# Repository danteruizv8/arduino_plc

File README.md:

# arduino_plc

Arduino compatible PLC board PCB.

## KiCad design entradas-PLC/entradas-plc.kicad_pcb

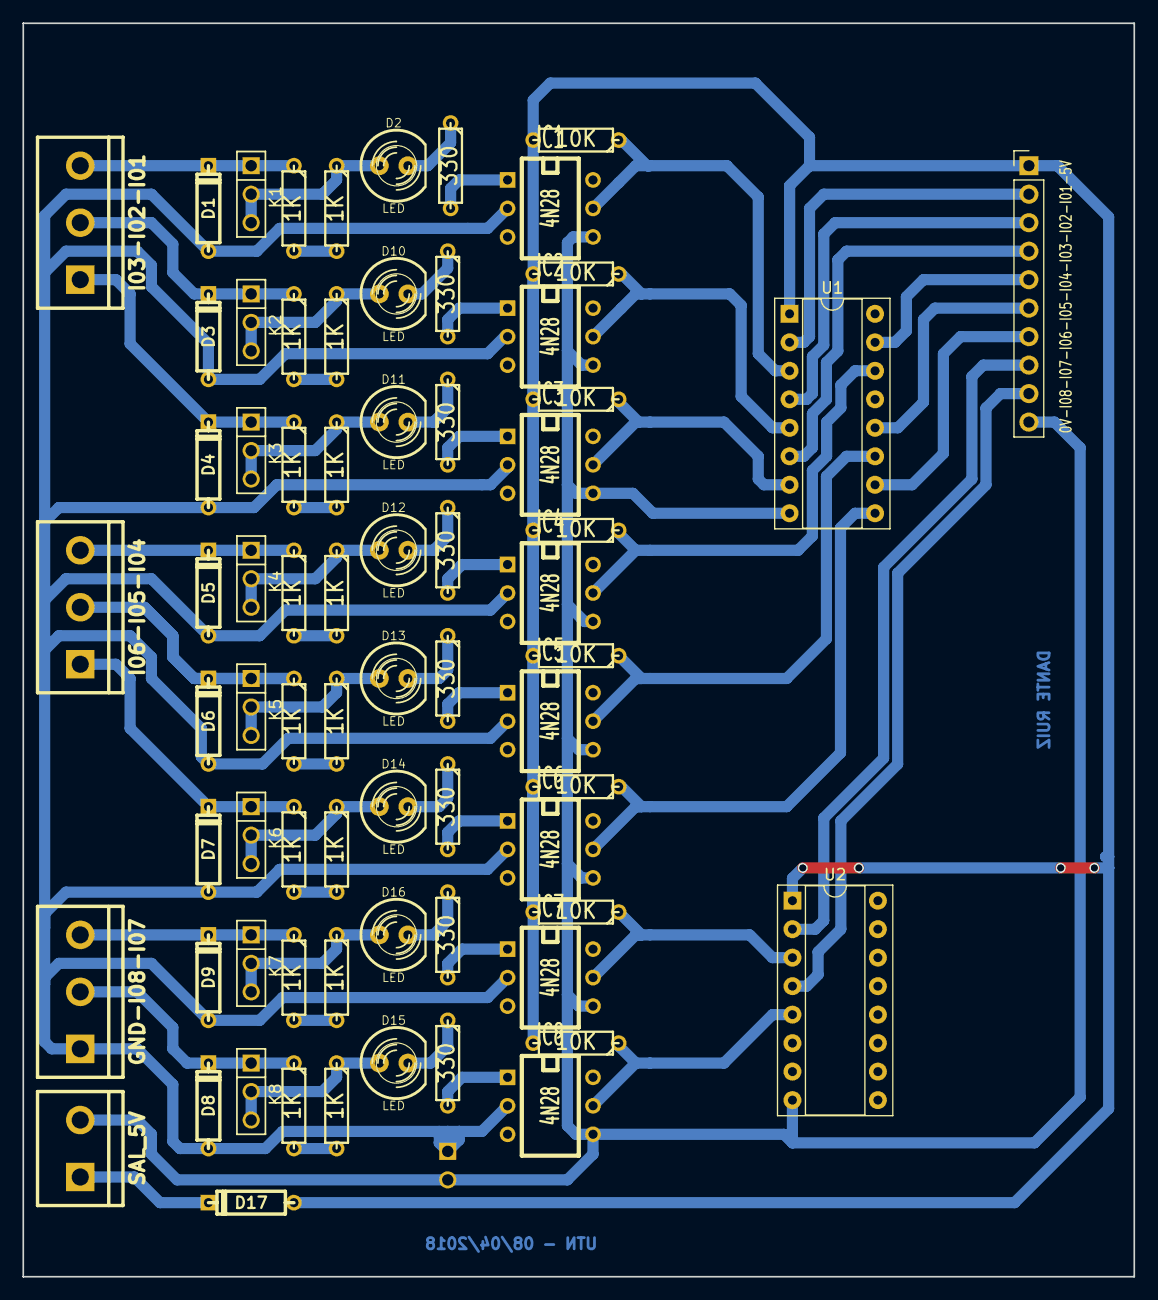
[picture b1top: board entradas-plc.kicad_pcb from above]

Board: 2 copper layers, 99.1 x 111.8 mm, 73 parts (1 on the bottom side), 60 nets.

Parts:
D1, D3, D4, D5, D6, D7, D8, D9: ZENER_24V; D3
D2, D10, D11, D12, D13, D14, D15, D16: LED; LED-5MM
D17: DIODE; D3
IC1, IC2, IC3, IC4, IC5, IC6, IC7, IC8: 4N28; DIP-6__300
J2: SIL10; Socket_Strip_Straight_1x10_Pitch2.54mm
K1, K2, K3, K4, K5, K6, K7, K8: CONN_3; PIN_ARRAY_3X1
K9: I03-I02-I01; bornier3
K10: I06-I05-I04; bornier3
K11: GND-I08-I07; bornier3
P1: SAL_5V; bornier2
P2: J_GND; PIN_ARRAY_2X1
R1, R5, R6, R7, R8, R9, R10, R11: 330; R3
R2, R12, R13, R14, R15, R16, R17, R18: 10K; R3
R3, R4, R19, R20, R21, R22, R23, R24, R25, R26, R27, R28, R29, R30, R31, R32: 1K; R3
U1, U2: 4049; DIP-16_W7.62mm_Socket

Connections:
Earth: IC1.4, IC2.4, IC3.4, IC4.4, IC5.4, IC6.4, IC7.4, IC8.4, J2.10, P1.2, P2.2, U1.8, U2.8
GND: D1.1, D3.1, D4.1, D5.1, D6.1, D7.1, D8.1, D9.1, IC1.2, IC2.2, IC3.2, IC4.2, IC5.2, IC6.2, IC7.2, IC8.2, K11.1, P2.1
unnamed: D1.2, K1.1, K9.3, R3.1
unnamed: D2.1, K1.2, K1.3, R23.1
unnamed: D2.2, R1.1
unnamed: D3.2, K2.1, K9.2, R4.1
unnamed: D4.2, K3.1, K9.1, R19.1
unnamed: D5.2, K4.1, K10.3, R20.1
unnamed: D6.2, K5.1, K10.2, R21.1
unnamed: D7.2, K6.1, K10.1, R22.1
unnamed: D8.2, K8.1, K11.2, R31.1
unnamed: D9.2, K7.1, K11.3, R32.1
unnamed: D10.1, K2.2, K2.3, R24.1
unnamed: D10.2, R5.1
unnamed: D11.1, K3.2, K3.3, R25.1
unnamed: D11.2, R6.1
unnamed: D12.1, K4.2, K4.3, R26.1
unnamed: D12.2, R7.1
unnamed: D13.1, K5.2, K5.3, R27.1
unnamed: D13.2, R8.1
unnamed: D14.1, K6.2, K6.3, R28.1
unnamed: D14.2, R9.1
unnamed: D15.1, K8.2, K8.3, R29.1
unnamed: D15.2, R10.1
unnamed: D16.1, K7.2, K7.3, R30.1
unnamed: D16.2, R11.1
unnamed: D17.2, P1.1
unnamed: IC1.1, R1.2
unnamed: IC1.5, R2.1, U1.3
unnamed: IC2.1, R5.2
unnamed: IC2.5, R12.1, U1.5
unnamed: IC3.1, R6.2
unnamed: IC3.5, R13.1, U1.7
unnamed: IC4.1, R7.2
unnamed: IC4.5, R14.1, U1.14
unnamed: IC5.1, R8.2
unnamed: IC5.5, R15.1, U1.11
unnamed: IC6.1, R9.2
unnamed: IC6.5, R16.1, U1.9
unnamed: IC7.1, R11.2
unnamed: IC7.5, R18.1, U2.3
unnamed: IC8.1, R10.2
unnamed: IC8.5, R17.1, U2.5
unnamed: J2.2, U1.2
unnamed: J2.3, U1.4
unnamed: J2.4, U1.6
unnamed: J2.5, U1.15
unnamed: J2.6, U1.12
unnamed: J2.7, U1.10
unnamed: J2.8, U2.2
unnamed: J2.9, U2.4
unnamed: R19.2, R25.2
unnamed: R20.2, R26.2
unnamed: R21.2, R27.2
unnamed: R22.2, R28.2
unnamed: R3.2, R23.2
unnamed: R4.2, R24.2
unnamed: R29.2, R31.2
unnamed: R30.2, R32.2
VCC: D17.1, J2.1, R2.2, R12.2, R13.2, R14.2, R15.2, R16.2, R17.2, R18.2, U1.1, U2.1

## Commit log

2020-12-30 Actualizar ENTRADAS, entradas-componentes.pdf y 23 más archivos...
